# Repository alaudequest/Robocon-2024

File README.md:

# Giới thiệu

Đế robot điều khiển 4 cụm bánh Swerve bằng chuẩn truyền thông CAN bus, mỗi cụm bánh bao gồm 1 bánh BLDC điều khiển đế robot tiến lùi và 1 động cơ DC dùng để xoay góc được điều khiển bởi node CAN STM32F103C8T6, các cụm bánh sẽ nhận lệnh từ node CAN main STM32F407VET để điều khiển hai động cơ

# Version (3.0.0)

Tài liệu hiện tại tương thích với version 3.x

README cụm bánh Swerve [NodeSwerve_F103](NodeSwerve_F103/README.md)

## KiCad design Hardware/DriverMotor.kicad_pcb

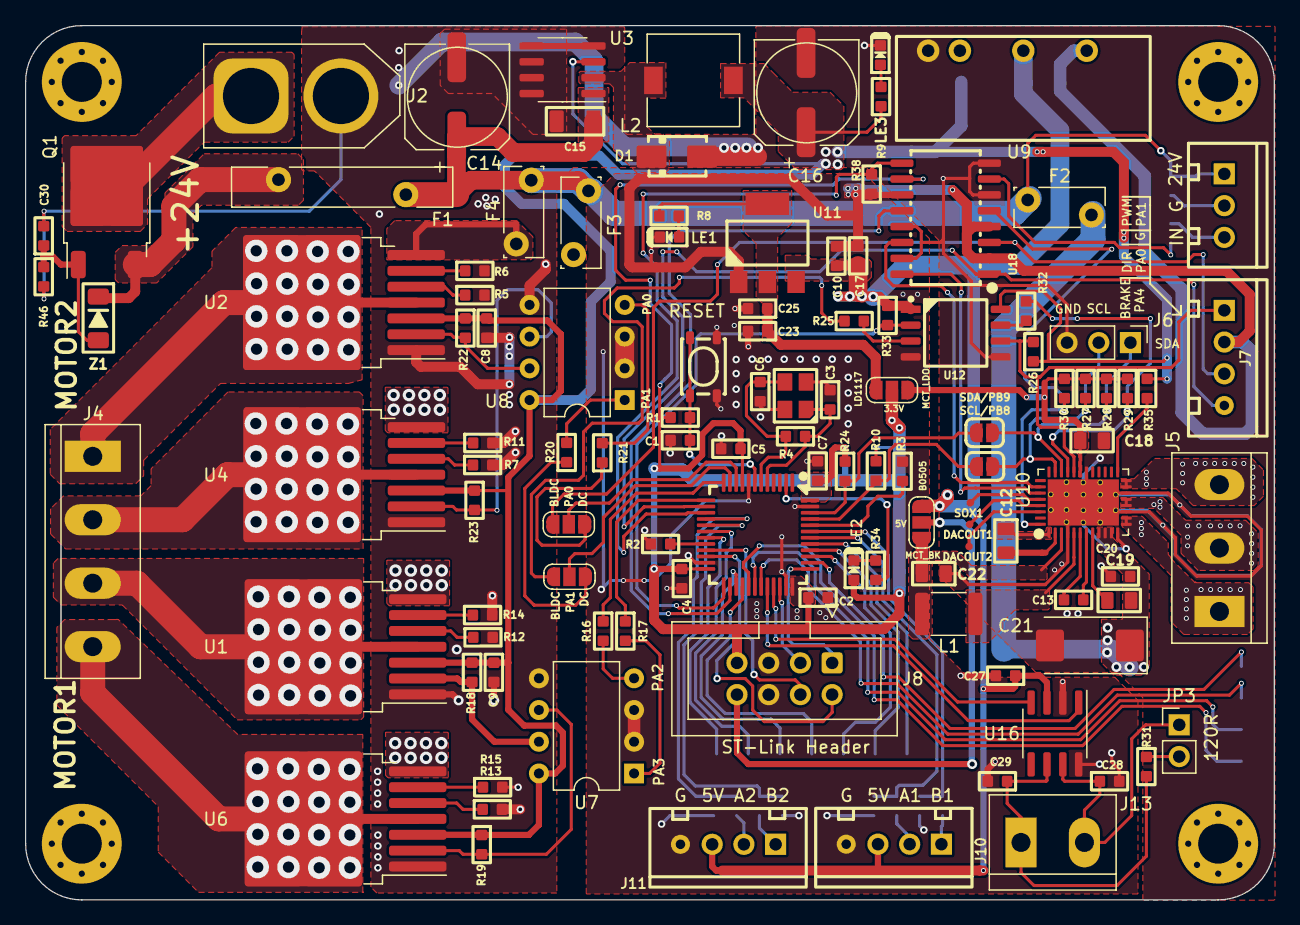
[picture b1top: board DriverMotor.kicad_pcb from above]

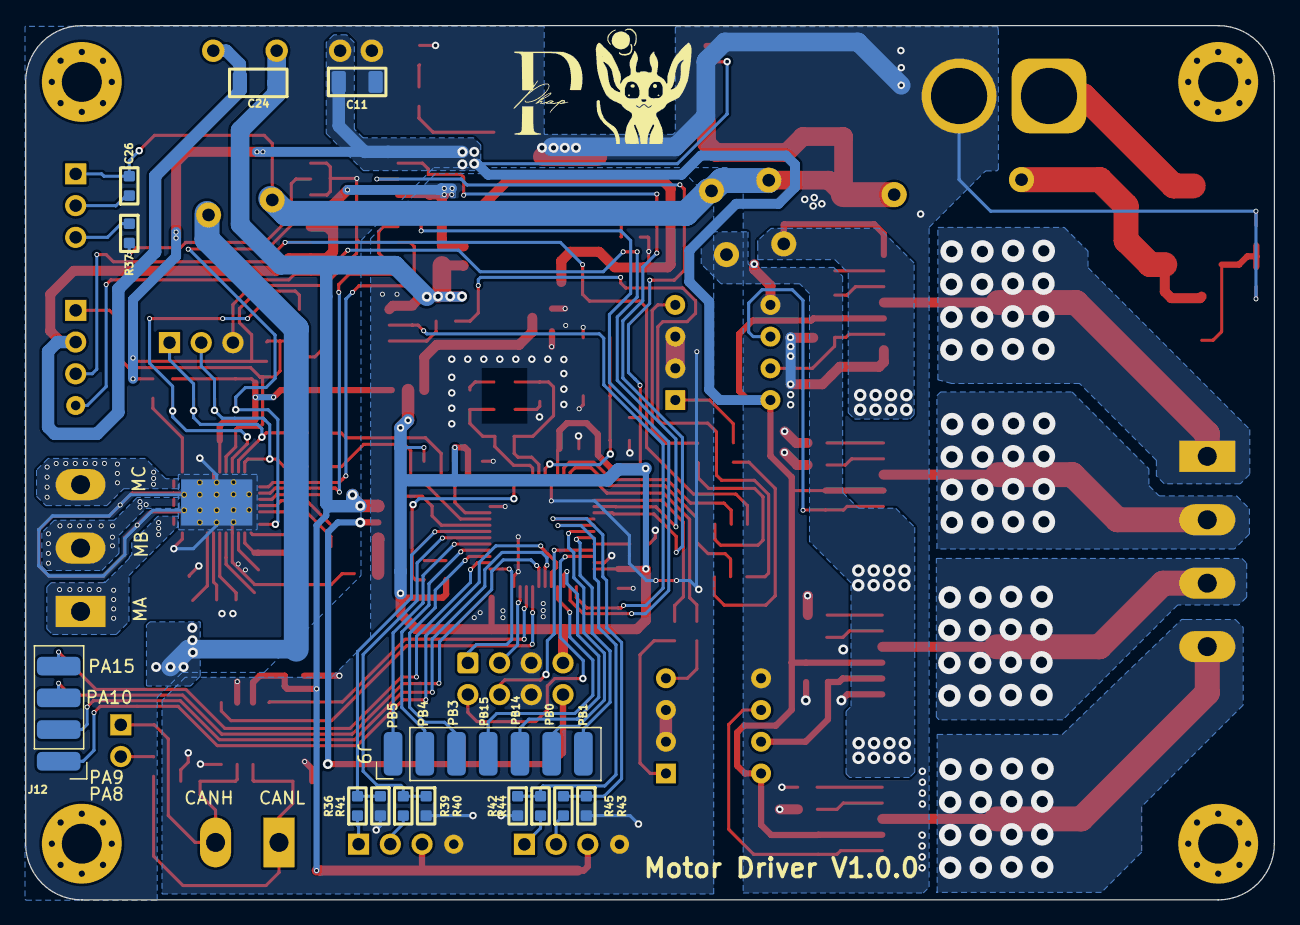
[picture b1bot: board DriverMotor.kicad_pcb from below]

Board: 2 copper layers, 100.0 x 70.0 mm, 130 parts (14 on the bottom side), 113 nets.

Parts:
C1: 10pF; C_0603
C2, C4, C5, C7, C8, C9, C10, C20, C25, C27, C30: 100nF; C_0603
C3, C6: 22pF; C_0603
C11: 4.7uF/16V; C_1206
C12, C18, C19, C22: 1uF; C_0805
C13: 47nF; C_0603
C14: 220uF/35V; CP-Alu-SMD-8x10.5mm
C15: 1uF; C_1206
C16: 470uF/16V; CP-Alu-SMD-8x10.5mm
C17, C23, C26: 10uF; C_0603
C21: 22uF/25V; CP_EIA-7343-15_Kemet-W_Pad2.25x2.55mm_HandSolder
C24: 10uF/10V; C_1206
C28, C29: 30pF; C_0603
D1: D_Diode; Package-Diode-D_SMA
DACOUT1, DACOUT2: TestPoint; TestPoint_Pad_D1.0mm
F1: 30V/5A; Fuse_Bourns_MF-RHT1000
F2: 30V/3A; Fuse_Bourns_MF-RG300
F3, F4: 30V/1.1A; Fuse_Bourns_MF-RG300
H1, H2, H3, H4: MountingHole; MountingHole_3.2mm_M3_Pad_Via
J1: Conn_01x03_Pin; Conn-Vert-THT-3P-2.54mm-S3B_XH_SM4_TB
J2: Screw_Terminal_01x02; Conn-Vert-THT-2P-7.20mm-XT60_F
J4: Screw_Terminal_01x04; TerminalBlock_bornier-4_P5.08mm
J5: Screw_Terminal_01x03; TerminalBlock_bornier-3_P5.08mm
J6: Screw_Terminal_01x03; PinHeader_1x03_P2.54mm_Vertical
J7: Conn_01x04_Male; Conn-Vert-THT-4P-2.54mm-S4B_XH_SM4_TB
J8: Conn_02x04_Odd_Even; IDC-Header_2x04_P2.54mm_Vertical
J9: Conn_01x07_Pin; Conn-Horz-SMD-7P-2.54mm-PinHeader
J10, J11: Screw_Terminal_01x04; Conn-Vert-THT-4P-2.54mm-S4B_XH_SM4_TB
J12: Conn_01x04_Male; Conn-Horz-SMD-4P-2.54mm-PinHeader
J13: Screw_Terminal_01x02; TerminalBlock_bornier-2_P5.08mm
JP3: SolderJumper_2_Open; PinHeader_1x02_P2.54mm_Vertical
L1: 47uH; L_1812_4532Metric
L2: 47uH; L_7.3x7.3_H4.5
LE1, LE2, LE3: Led; LED_0603
Q1: P_Mosfet; TO-252-2
R1, R2: 10k; R_0603
R3, R5, R6, R7, R11, R12, R13, R14, R15, R18, R19, R22, R23: 10K; R_0603
R4: 1M; R_0603
R8: 1k; R_0603
R9, R26, R33, R35, R36, R37, R38, R41, R44, R45: 1K; R_0603
R10, R24: 4k7; R_0603
R16, R17, R20, R21: 240R; R_0603
R25, R32: 330R; R_0603
R27, R28, R29, R30: 5K1; R_0603
R31: 120R; R_0603
R34: 2K2; R_0603
R39, R40, R42, R43: 2K; R_0603
R46: 100k; R_0603
S1, S2, S3, S4: SolderJump3P; SolderJumper-3_P1.3mm_Open_RoundedPad1.0x1.5mm_NumberLabels
SCL/PB8: SolderJumper_2_Open; SolderJumper-2_P1.3mm_Open_RoundedPad1.0x1.5mm
SDA/PB9: SolderJumper_2_Open; SolderJumper-2_P1.3mm_Open_RoundedPad1.0x1.5mm
SOX1: TestPoint; TestPoint_Pad_D1.0mm
SW1: SW_Push; ButtonPush-Vert-SMD-4P-SPST_PTS810
U1, U2, U4, U6: TO-263-7_TabPin8
U3: XL1509-5.0; SOIC-8_3.9x4.9mm_P1.27mm
U5: MCU_STM32F103C8Tx; Package-IC-LQFP-48P-7x7mm-P0.5mm
U7, U8: HCPL-2631; DIP-8_W7.62mm
U9: B0505S; PowerSupply-DCDC-Isolate-2W-BxxxxS
U10: MCT8316; VQFN-40-1EP_7x7mm_P0.5mm_EP5.7x3.7mm_ThermalVias
U11: LD1117; SOT233
U12: ISO7721DR; SOIC-8_5.23x5.23mm_P1.27mm
U16: TJA1051T; SOIC-8_3.9x4.9mm_P1.27mm
U18: SOIC-16W_5.3x10.2mm_P1.27mm
Y1: 8Mhz; Crystal-SMD-4P-3.2x2.6mm-3225
Z1: 15V; Package-Diode-D_MiniMELF

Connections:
+3V3: C23.1, C25.1, R8.1, S2.1, U11.2 (VO)
+5V: C10.1, C17.1, C24.1, C27.1, J10.3, J11.3, R33.1, S1.1, U9.4 (Vout), U11.3 (VI), U12.1 (VCC1), U16.3 (VCC)
+5VA: J8.8, S1.2
+24V: J2.1, Q1.2 (D)
/BTS7960/+5V_CS: C8.1, C9.1, C11.1, C16.1, L2.1, R9.1, R18.1, R19.1, R22.1, R23.1, R26.1, R35.1, U1.3 (INH), U2.3 (INH), U3.3 (FB), U4.3 (INH), U6.3 (INH), U7.8 (VCC), U8.8 (VCC), U9.2 (Vin), U12.8 (VCC2)
/BTS7960/+24V_CS: C14.1, C15.1, C26.2, F1.2, F2.1, F3.1, F4.1, J1.1, U3.1 (VIN)
/BTS7960/+24V_M1: F3.2, U1.7 (VS), U6.7 (VS)
/BTS7960/+24V_M2: F4.2, U2.7 (VS), U4.7 (VS)
/BTS7960/BTS.PWM_L1: R17.1, U5.13 (PA3/USART2_RX/ADC12_IN3/TIM2_CH4)
/BTS7960/BTS.PWM_L2: R20.1, S3.1
/BTS7960/BTS.PWM_R1: R16.1, U5.12 (PA2/USART2_TX/ADC12_IN2/TIM2_CH3)
/BTS7960/BTS.PWM_R2: R21.1, S4.1
/BTS7960/En.EnA_1: R40.1, R41.2, U5.42 (PB6/USART1_TX/I2C1_SCL/TIM4_CH1)
/BTS7960/En.EnA_2: R43.1, R45.2, U5.16 (PA6/SPI1_MISO/ADC12_IN6/TIM3_CH1)
/BTS7960/En.EnB_1: R36.2, R39.1, U5.43 (PB7/USART1_RX/I2C1_SDA/TIM4_CH2)
/BTS7960/En.EnB_2: R42.1, R44.2, U5.17 (PA7/SPI1_MOSI/ADC12_IN7/TIM3_CH2)
/BTS7960/Motor_L1: J4.3, U1.4 (OUT), U1.8 (TAB)
/BTS7960/Motor_L2: J4.1, U2.4 (OUT), U2.8 (TAB)
/BTS7960/Motor_R1: J4.4, U6.4 (OUT), U6.8 (TAB)
/BTS7960/Motor_R2: J4.2, U4.4 (OUT), U4.8 (TAB)
/BTS7960/PWM_DC_L1: R18.2, U1.2 (IN), U7.7 (VO1)
/BTS7960/PWM_DC_L2: R22.2, U2.2 (IN), U8.7 (VO1)
/BTS7960/PWM_DC_R1: R19.2, U6.2 (IN), U7.6 (VO2)
/BTS7960/PWM_DC_R2: R23.2, U4.2 (IN), U8.6 (VO2)
/MCT8316/+3V3_MCU: C2.1, C4.1, C5.1, C7.1, J8.7, LE2.1, R1.1, R10.1, R24.1, S2.2, U5.9 (VDDA), U5.24 (VDD), U5.36 (VDD), U5.48 (VDD), U18.10
/MCT8316/AVDD: C18.1, R27.1, R28.1, R29.1, R30.1, S2.3, U10.27 (AVDD)
/MCT8316/BUCK: C22.2, L1.1, S1.3, U10.3 (FB_BK)
/MCT8316/DVDD: C12.1, U10.1 (DVDD)
/MCT8316/MA: J5.1, U10.13 (OUTA), U10.14 (OUTA)
/MCT8316/MB: J5.2, U10.16 (OUTB), U10.17 (OUTB)
/MCT8316/MC: J5.3, U10.19 (OUTC), U10.20 (OUTC)
/MCT8316/MCT.BRAKE: J7.4, U5.14 (PA4/SPI1_NSS/USART2_CK/ADC12_IN4), U18.1
/MCT8316/MCT.DIR: J7.3, S4.3, U18.3
/MCT8316/MCT.FAULT: U5.26 (PB13/SPI2_SCK/USART3_CTS/TIM1_CH1N), U18.12
/MCT8316/MCT.FG: R33.2, U5.25 (PB12/SPI2_NSS/I2C2_SMBAI/USART3_CK/TIM1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), U12.2 (OUTA)
/MCT8316/MCT.PWM: R25.1, S3.3
/MCT8316/MCT.SCL: R10.2, SCL/PB8.1 (A), U5.45 (PB8/TIM4_CH3/I2C1_SCL/CANRX)
/MCT8316/MCT.SDA: R24.2, SDA/PB9.1 (A), U5.46 (PB9/TIM4_CH4/I2C1_SDA/CANTX)
/MCT8316/MCT_BRAKE: U10.35 (BRAKE), U18.16
/MCT8316/MCT_DACOUT1: DACOUT1.1, U10.37 (DACOUT1)
/MCT8316/MCT_DACOUT2: DACOUT2.1, U10.38 (DACOUT2)
/MCT8316/MCT_DIR: U10.34 (DIR), U18.14
/MCT8316/MCT_FAULT: R30.2, U10.40 (nFAULT), U18.5
/MCT8316/MCT_FG: R29.2, R32.2, U10.29 (FG)
/MCT8316/MCT_SCL: J6.2, R27.2, SCL/PB8.2 (B), U10.31 (SCL)
/MCT8316/MCT_SDA: J6.1, R28.2, SDA/PB9.2 (B), U10.30 (SDA)
/MCT8316/MCT_SOX: SOX1.1, U10.36 (DACOUT2/SOX)
/MCT8316/PA5: R38.1, U5.15 (PA5/SPI1_SCK/ADC12_IN5), U18.9
/MCT8316/PWM_BLDC: J7.1, R26.2, U10.28 (SPEED/WAKE), U12.6 (OUTB)
/MCT8316/SW_BUCK: L1.2, U10.5 (SW_BK)
/MCT8316/VM: C19.2, C20.2, C21.1, F2.2, U10.9 (VM), U10.10 (VM), U10.11 (VM)
/Power Supply/S: F1.1, Q1.3 (S), Z1.2
/Power Supply/XL1509_OUT: D1.2, L2.2, U3.2 (OUT)
/STM32F103/CANRX: U5.32 (PA11/USART1_CTS/CANRX/USBDM/TIM1_CH4), U16.1 (TXD)
/STM32F103/CANTX: U5.33 (PA12/USART1_RTS/CANTX/USBDP/TIM1_ETR), U16.4 (RXD)
/STM32F103/MCU_PA0: S4.2, U5.10 (PA0/WKUP/USART2_CTS/ADC12_IN0/TIM2_CH1_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)
/STM32F103/MCU_PA1: S3.2, U5.11 (PA1/USART2_RTS/ADC12_IN1/TIM2_CH2)
/STM32F103/OSC_IN: C3.2, R4.1, U5.5 (PD0/OSC_IN), Y1.1
/STM32F103/OSC_OUT: C6.1, R4.2, U5.6 (PD1/OSC_OUT), Y1.3
/STM32F103/PA8: J12.1, U5.29 (PA8/USART1_CK/TIM1_CH1/MCO)
/STM32F103/PA9: J12.2, U5.30 (PA9/USART1_TX/TIM1_CH2)
/STM32F103/PA10: J12.3, U5.31 (PA10/USART1_RX/TIM1_CH3)
/STM32F103/PA15: J12.4, U5.38 (PA15/JTDI)
/STM32F103/PB0: J9.6, U5.18 (PB0/ADC12_IN8/TIM3_CH3/TIM1_CH2N)
/STM32F103/PB1: J9.7, U5.19 (PB1/ADC12_IN9/TIM3_CH4/TIM1_CH3N)
/STM32F103/PB3: J9.3, U5.39 (PB3/JTDO/TIM2_CH2/TRACESWO/SPI1_SCK)
/STM32F103/PB4: J9.2, U5.40 (PB4/JNTRST/TIM3_CH1/SPI1_MISO)
/STM32F103/PB5: J9.1, U5.41 (PB5/TIM3_CH2/SPI1_MOSI/I2C1_SMBAI)
/STM32F103/PB14: J9.5, U5.27 (PB14/SPI2_MISO/USART3_RTS/TIM1_CH2N)
/STM32F103/PB15: J9.4, U5.28 (PB15/SPI2_MOSI/TIM1_CH3N)
/STM32F103/PC13: R34.2, U5.2 (PC13/TAMPER-RTC)
/STM32F103/RST: C1.2, R1.2, SW1.1, U5.7 (NRST)
/STM32F103/RX_LOG: J8.2, U5.22 (PB11/I2C2_SDA/USART3_RX/TIM2_CH4)
/STM32F103/SWCLK: J8.1, U5.37 (PA14/JTCK/SWCLK)
/STM32F103/SWDIO: J8.3, U5.34 (PA13/JTMS/SWDIO)
/STM32F103/TX_LOG: J8.4, U5.21 (PB10/I2C2_SCL/USART3_TX/TIM2_CH3)
/TJA1050/CANH: C28.1, J13.2, JP3.1 (A), U16.7 (CANH)
/TJA1050/CANL: C29.1, J13.1, R31.2, U16.6 (CANL)
GND: C1.1, C2.2, C3.1, C4.2, C5.2, C6.2, C7.2, C10.2, C17.2, C23.2, C24.2, C25.2, C27.2, C28.2, C29.2, J7.2, J8.5, J8.6, J10.4, J11.4, LE1.2, R2.1, R3.1, R38.2, R39.2, R40.2, R42.2, R43.2, SW1.2, U5.8 (VSSA), U5.23 (VSS), U5.35 (VSS), U5.47 (VSS), U7.2 (C1), U7.3 (C2), U8.2 (C1), U8.3 (C2), U9.3 (GNDout), U11.1 (GND), U12.4 (GND1), U16.2 (GND), U16.8 (S), U18.2, U18.4, U18.11, Y1.2, Y1.4
GNDD: C8.2, C9.2, C11.2, C14.2, C15.2, C16.2, C18.2, C20.1, C21.2, C22.1, C30.2, D1.1, J2.2, J6.3, LE3.2, R5.2, R6.2, R7.2, R11.2, R12.2, R13.2, R14.2, R15.2, R46.2, U1.1 (GND), U2.1 (GND), U3.4 (~EN), U3.5 (GND), U3.6 (GND), U3.7 (GND), U3.8 (GND), U4.1 (GND), U6.1 (GND), U7.5 (GND), U8.5 (GND), U9.1 (GNDin), U10.4 (GND_BK), U10.12 (PGND), U10.15 (PGND), U10.18 (PGND), U10.26 (AGND), U10.41 (ThermalPad), U12.5 (GND2), U18.6, U18.8, U18.13, U18.15
unnamed: C26.1, J1.2
unnamed: J1.3, R37.1
unnamed: J10.1, R36.1
unnamed: J10.2, R41.1
unnamed: J11.1, R44.1
unnamed: J11.2, R45.1
unnamed: JP3.2 (B), R31.1
unnamed: LE1.1, R8.2
unnamed: LE2.2, R34.1
unnamed: LE3.1, R9.2
unnamed: C30.1, Q1.1 (G), R46.1, Z1.1
unnamed: R37.2, U18.7
unnamed: R14.1, U1.6 (IS)
unnamed: R12.1, U1.5 (SR)
unnamed: R6.1, U2.6 (IS)
unnamed: R5.1, U2.5 (SR)
unnamed: R11.1, U4.6 (IS)
unnamed: R7.1, U4.5 (SR)
unnamed: R3.2, U5.44 (BOOT0)
unnamed: R2.2, U5.20 (PB2/BOOT1)
unnamed: R15.1, U6.6 (IS)
unnamed: R13.1, U6.5 (SR)
unnamed: R17.2, U7.1 (A1)
unnamed: R16.2, U7.4 (A2)
unnamed: R20.2, U8.1 (A1)
unnamed: R21.2, U8.4 (A2)
unnamed: C19.1, U10.8 (CP)
unnamed: C13.2, U10.7 (CPH)
unnamed: C13.1, U10.6 (CPL)
unnamed: C12.2, U10.2 (DGND)
unnamed: R35.2, U10.21 (DRVOFF)
unnamed: R32.1, U12.7 (INA)
unnamed: R25.2, U12.3 (INB)

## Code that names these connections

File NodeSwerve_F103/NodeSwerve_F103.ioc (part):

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Mcu.Name=STM32F103C(8-B)Tx
Mcu.Package=LQFP48
Mcu.UserName=STM32F103C8Tx
PA0-WKUP.GPIOParameters=GPIO_Label
PA0-WKUP.GPIO_Label=BLDC_DIR
PA0-WKUP.Signal=GPIO_Output
PA1.Signal=S_TIM2_CH2
PA10.Mode=Asynchronous
PA10.Signal=USART1_RX
PA11.Mode=CAN_Activate
PA11.Signal=CAN_RX
PA12.Mode=CAN_Activate
PA12.Signal=CAN_TX
PA13.Mode=Serial_Wire
PA13.Signal=SYS_JTMS-SWDIO
PA14.Mode=Serial_Wire
PA14.Signal=SYS_JTCK-SWCLK
PA2.Signal=S_TIM2_CH3
PA3.Signal=S_TIM2_CH4
PA4.GPIOParameters=GPIO_Label
PA4.GPIO_Label=BLDC_BRAKE
PA4.Signal=GPIO_Output
PA5.GPIOParameters=GPIO_Label
PA5.GPIO_Label=Sensor_Home
PA5.Signal=GPIO_Input
PA6.Signal=S_TIM3_CH1
PA7.Signal=S_TIM3_CH2
PA9.Mode=Asynchronous
PA9.Signal=USART1_TX
PB3.GPIOParameters=GPIO_Label
PB3.GPIO_Label=UserLED
PB3.Signal=GPIO_Output
PB6.Signal=S_TIM4_CH1
PB7.Signal=S_TIM4_CH2
PD0-OSC_IN.Mode=HSE-External-Oscillator
PD0-OSC_IN.Signal=RCC_OSC_IN
PD1-OSC_OUT.Mode=HSE-External-Oscillator
PD1-OSC_OUT.Signal=RCC_OSC_OUT
RCC.SYSCLKFreq_VALUE=72000000
RCC.SYSCLKSource=RCC_SYSCLKSOURCE_PLLCLK
board=custom

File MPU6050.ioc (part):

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Mcu.Name=STM32F103C(8-B)Tx
Mcu.Package=LQFP48
Mcu.UserName=STM32F103C8Tx
PA10.Mode=Asynchronous
PA10.Signal=USART1_RX
PA13.Mode=Serial_Wire
PA13.Signal=SYS_JTMS-SWDIO
PA14.Mode=Serial_Wire
PA14.Signal=SYS_JTCK-SWCLK
PA9.Mode=Asynchronous
PA9.Signal=USART1_TX
PB0.GPIOParameters=GPIO_Label
PB0.GPIO_Label=Ready
PB0.Signal=GPIO_Output
PB1.GPIOParameters=GPIO_Label
PB1.GPIO_Label=Data
PB1.Signal=GPIO_Output
PB13.GPIOParameters=GPIO_Label
PB13.GPIO_Label=UserGreenLED
PB13.Signal=GPIO_Output
PB14.Mode=PWM Generation2 CH2N
PB14.Signal=TIM1_CH2N
PB5.GPIOParameters=GPIO_Label,GPIO_ModeDefaultEXTI
PB5.GPIO_Label=UserBtn
PB5.GPIO_ModeDefaultEXTI=GPIO_MODE_IT_FALLING
PB5.Signal=GPXTI5
PB6.Mode=I2C
PB6.Signal=I2C1_SCL
PB7.Mode=I2C
PB7.Signal=I2C1_SDA
PB8.GPIOParameters=GPIO_Label
PB8.GPIO_Label=MPU_INT
PB8.Signal=GPXTI8
PD0-OSC_IN.Mode=HSE-External-Oscillator
PD0-OSC_IN.Signal=RCC_OSC_IN
PD1-OSC_OUT.Mode=HSE-External-Oscillator
PD1-OSC_OUT.Signal=RCC_OSC_OUT
RCC.SYSCLKFreq_VALUE=72000000
RCC.SYSCLKSource=RCC_SYSCLKSOURCE_PLLCLK
board=custom

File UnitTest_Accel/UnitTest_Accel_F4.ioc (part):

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Mcu.Name=STM32F407V(E-G)Tx
Mcu.Package=LQFP100
Mcu.UserName=STM32F407VETx
PA13.Mode=Serial_Wire
PA13.Signal=SYS_JTMS-SWDIO
PA14.Mode=Serial_Wire
PA14.Signal=SYS_JTCK-SWCLK
PA15.Signal=S_TIM2_CH1_ETR
PA2.Signal=S_TIM5_CH3
PA3.Signal=S_TIM5_CH4
PA8.Signal=S_TIM1_CH1
PA9.Signal=S_TIM1_CH2
PB3.Signal=S_TIM2_CH2
PE14.GPIOParameters=GPIO_PuPd,GPIO_Label
PE14.GPIO_Label=Checkpoint
PE14.GPIO_PuPd=GPIO_PULLUP
PE14.Signal=GPXTI14
PH0-OSC_IN.Mode=HSE-External-Oscillator
PH0-OSC_IN.Signal=RCC_OSC_IN
PH1-OSC_OUT.Mode=HSE-External-Oscillator
PH1-OSC_OUT.Signal=RCC_OSC_OUT
RCC.HSE_VALUE=8000000
RCC.SYSCLKFreq_VALUE=168000000
RCC.SYSCLKSource=RCC_SYSCLKSOURCE_PLLCLK
board=custom

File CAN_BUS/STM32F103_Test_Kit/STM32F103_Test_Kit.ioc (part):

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Mcu.Name=STM32F103C(8-B)Tx
Mcu.Package=LQFP48
Mcu.UserName=STM32F103C8Tx
PA13.Mode=Serial_Wire
PA13.Signal=SYS_JTMS-SWDIO
PA14.Mode=Serial_Wire
PA14.Signal=SYS_JTCK-SWCLK
PB8.Signal=S_TIM4_CH3
PB9.Signal=S_TIM4_CH4
PC13-TAMPER-RTC.GPIOParameters=GPIO_Label
PC13-TAMPER-RTC.GPIO_Label=USER_LED
PC13-TAMPER-RTC.Signal=GPIO_Output
PD0-OSC_IN.Mode=HSE-External-Oscillator
PD0-OSC_IN.Signal=RCC_OSC_IN
PD1-OSC_OUT.Mode=HSE-External-Oscillator
PD1-OSC_OUT.Signal=RCC_OSC_OUT
RCC.SYSCLKFreq_VALUE=72000000
RCC.SYSCLKSource=RCC_SYSCLKSOURCE_PLLCLK
board=custom

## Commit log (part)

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2023-11-18 Update node F1: remove function pointer of SetHome
2023-11-18 Updated 19/11/2023
2023-11-19 Test event group OK
2023-11-19 Initial Function of Odometry
2023-11-19 Update: F4 measure processing time of function RTR_SpeedAngle from begin to end
2023-11-20 First function of Swerve Odometry
2023-11-23 Test eventgroup to send and receive 1 node once time, repeat 4 times with total time is 1.1ms, slower than for loop of NOP, reverse for future use
2023-11-24 Add CAN_RTR_Encx4BLDC_AngleDC for RTR encoder X4 count of BLDC and AngleDC, not use CAN_SpeedBLDC_AngleDC because the affect to input Motor API, ignore language setting xml
2023-11-28 build MPU6050 lib.cpp with write and read method, test WHO_AM_I register OK, can not read temperature value
2023-11-28 fix: method Write, can read temperature data and config sensor registers
2023-11-29 Update + feature: change method name of MPU, add get set clock source
2023-11-29 Adding ConfigRegister struct to save config MPU data after init, easy to dev methods of MPU6050 config register, can be read GyroZ data by changing clock source from internal to PLL_XGYRO
2023-11-30 feature: Read Raw each axis and 6 axis OK
2023-11-30 Change offset not affect much
2023-12-01 Adding UART to send to PC in main.cpp, remove this pointer of class MPU6050 in MPU6050.h
2023-12-02 add this->i2c instead of i2c in MPU::init
2023-12-03 nothing
2023-12-06 Update: Seperate CANCTRL_MODE_MOTOR_SPEED_ANGLE and CANCTRL_MODE_NODE_REQ_SPEED_ANGLE, update README for RTR mode
    CAN_FuncHandle:
    + Thêm cặp hàm Get/Set EncoderX4CountBLDC_Angle
    CAN_Control:
    + Thay đổi thứ tự các ID trong bộ lọc list để khớp với datasheet
    BoardParameter:
    + Xóa hàm brd_GetCurrentCountBLDC()
2023-12-08 Add LogPort class to use template for plotter
2023-12-09 Update: get 6 axis, calib raw accel
2023-12-13 Update: Can read FIFO interrupt, not handle properly
    - Adding Timer 2, not use yet
    - fifoHandle not optimize, temporary use to test interrupt feature
2023-12-25 Done with odometry and Forward kinematic
2024-01-13 Update: Config pinout
2024-01-13 Add project Actuator_GetShootingBall
2024-01-13 Add .gitignore
2024-01-15 remove test project
2024-01-17 Update: Add and config Encoder library. Issues: Encoder library not support for interrupt type -> need to rewrite.
2024-01-17 Update: Config new pinout and commented issues
2024-01-17 Done point to point algorithm
2024-01-17 Setup pwm Channel in BoardParameter lib
2024-01-18 Bug Encoder Gun 1
2024-01-19 First commit, not use old board, commit to switch to other branch
2024-01-19 worked pure pursuilt algorithm
2024-01-20 test shoot without PID
2024-01-20 Trajec Planning function
2024-01-21 Issue: Cấp xung pwm cho động cơ bắn nhưng đông cơ không quay (bts hỏng) Update: Thêm điều kiện để quay rulo bóng và rulo súng
2024-01-21 NamDHay
2024-01-22 Add get&set value function
2024-01-22 new actuator mergre
2024-01-22 fix HardFault Handle
2024-01-23 Done 1 turn get wheeds
2024-01-23 Up-to-date Valve trigger and shooting ball, control robot to catch and drop seedling
2024-01-23 New feature: Seperate encoder mode and interrupt
2024-01-23 Add encoder init to brd_Init
2024-01-23 get wheed two turns
2024-01-23 MPU read ok
2024-01-23 Add BNO08x Arduino to project, remove unesscessary files
2024-01-24 Fix a few type errors
2024-01-24 Complete
2024-01-24 Complete low level Driver
2024-01-24 Successfully read and write to app
2024-01-24 steady V1
2024-01-25 ignore .vscode
2024-01-25 Need to update
2024-01-26 Update IMU code
2024-01-26 Update: add command list, AppProtocol and ParamPID struct
2024-01-26 Update: PD_On and Off, merging 50f13e65 commit from origin HoangTrajecPlanning branch
2024-01-26 Add CAN_FuncHandle
2024-01-27 Steady V2
2024-01-28 Still unstable
2024-01-30 BNO DMA
2024-02-01 Pose estimation
2024-02-01 Sai cmnr
2024-02-03 Add Gun Parameter and function handle
2024-02-03 Add RTR Handle and Shoot queue
2024-02-04 Add function to control rulo get balls and stop all motor on gun module
2024-02-04 Complete control motor part -> need to test CANBus
2024-02-06 Steady before add shoot
2024-02-06 Move CAN lib to main F407
2024-02-06 Add Cmake
2024-02-06 Update new function
2024-02-07 Change name AppProtocol to FrameData, update small change
2024-02-07 Remove unused ID
2024-02-07 remove vscode
2024-02-07 SteadyShoot
2024-02-08 Steady and shoot
2024-02-08 Update CAN folder from HoangSteadyV2
2024-02-08 2ndShoot
2024-02-10 Steady Mung 1
2024-02-18 Last update at Release frist wheed
2024-02-18 Add Break to serveral case
2024-02-18 Small Fixed for estimation
2024-02-22 Remove Rotary DC and add software timer to calculate PID
2024-02-25 Fix Stupid defined and if condition
2024-02-25 Remove software timer function and use xTaskGetTickCount to make delay
2024-02-26 Small clean
2024-02-28 small change
2024-03-14 Code work with Phat
2024-03-15 fix: remove language.settings and change cal_absF to static
2024-03-16 Get and Put Ball on AutoRobot
2024-03-17 Refactor: trajectory plainning library and manual set, not compile yet
2024-03-18 docs: move LogData to new folder Communication, add example code
2024-03-18 feat: ParameterSetting and config path to inc and src of Communication folder to project
2024-03-18 fix: QueueReceive, increase osDelay in InverseKinematic task
2024-03-18 fix: increase OdoHandle task stack size to 256 prevent stack overflow, test success Trajectory and Manual Set with 3 settings
2024-03-20 Add PE12 Forklift sensor interrupt
2024-03-20 Refactor BallTransferToSilo from PutBall module
2024-03-20 7 out of 10 ball sucessed
2024-03-21 feat: add HAL_TIM_start for pwm and encoder channel, add func get encoderX4 from forklift encoder
2024-03-21 add UART2, pwm channel and encoder for forklift motor and rulo, change name task RTOS, test actuator robot2
2024-03-21 GetBall Succeed 90%
2024-03-22 Update GetBall
2024-03-23 Update: change process control API to chassis control API
2024-03-23 FloatingEncOk
2024-03-23 Code a Loc train
2024-03-24 feat <Robot1_Gun_Actuator>:Add Shootball handle to Main_F407 and test case for it
2024-03-24 clean up all task, prepare to code Actuator task
2024-03-24 Add sensor interrupt config from cubeMX
2024-03-24 feat: add NVIC config for sensor ball push up
2024-03-24 update: test both arm catch and release rice
2024-03-24 Chu trinh lay 2 trai banh hoi on dinh
2024-03-24 fix: can not control bts
2024-03-24 feat <Robot1_Gun&BallConveyor>: Acceleration gun
2024-03-24 Steady get 2 ball and backhome
2024-03-25 Done kinematic
2024-03-25 Get 2 Ball 95%
2024-03-26 Succeed Merge PutBall and Sensor ADC
2024-03-27 PID with A Loc
2024-03-28 Updated code with a Loc
2024-03-28 Code skeleton
2024-03-28 fix : remove Actuator_GetShootBall
2024-03-28 remove unnecessary file
2024-03-30 Link new library to F1 project
2024-03-30 feat: Add AppInterface library
2024-03-30 Add CRC16 and seperate AppInterface to Communication folder
2024-03-30 add ArgumentOfCommandList_t, tx and rx buffer change to pointer, fix variable name to compile code, add comments
2024-03-30 Add PID tuning for 2 guns
2024-04-01 Steady get 2 ball and back home
2024-04-02 feat: Control BLDC and DC with PID via app interface
2024-04-02 feat: adding send relay command status of board at init
2024-04-03 Optimize Angle now available at slave
2024-04-03 Clean up Algorimth code in main.c
2024-04-03 New API for point to point and Angle rotate algorithm
2024-04-04 Hoang Merge complete part 1
2024-04-04 No Hardfault update
2024-04-04 reapply app interface from node swerve, change Commandlist
2024-04-04 feat: Place init code(CAN and valve) in int main instead of each task, add valve_OutputAllPin to control by app
2024-04-04 Test valve output with app OK
2024-04-05 App check if brdID is not zero
2024-04-05 Update commandlist for node swerve
2024-04-05 Add #define board in AppInterface
2024-04-05 Add define macro for each board selected
2024-04-07 feat:turn PID off and break pin on at specific speed
2024-04-07 feat: Add CAN untangle BLDC
2024-04-07 feat: untangle bldc from app
2024-04-07 feat: add untangleBLDC feature on main.c
2024-04-07 feat: Add AngleOptimizer and fix switch case SetHome and UntangleBLDC
2024-04-08 fix library reference
2024-04-08 feat: add jumpToError, MakeFrame_2 and reset AppInterface
2024-04-08 feat: Hanlde CurrentSpeedBLDC and CurrentAngleDC hande, reset encoder count instead of turn off timer
2024-04-08 Update AppInterface module from Khoa_AppInterface_NodeSwerve branch to MainF407 project
2024-04-08 Accelerate and run at 6000rpm
2024-04-09 feat: hanlde RuloShootBall TargetSpeed
2024-04-09 Test Gun ok
2024-04-10 Added Angle Optimizer for Node
2024-04-10 Fix file in PID_Swerve module
2024-04-10 small fix for board ID
2024-04-10 small change on kinematic
2024-04-11 Fixed Angle Optimizer code
2024-04-11 Fixed Limit output for DC
2024-04-11 Added new limit for DC Swerve
2024-04-11 Add untangle for slave
2024-04-11 Add Motor and ActuatorGun library from NamDHay_Robot1_ShootBall
2024-04-11 Add buzzer
2024-04-11 Fix: pin E5 E6 to GPIO output, Start getball and stop get ball, test get ball OK
2024-04-11 feat: Add PID for rulo shooting ball, not test
2024-04-11 fixed main ADC code
2024-04-11 feat: add accel rulo speed and test with app ok
2024-04-11 Small fix for easier test code
2024-04-11 Fix Angle PID controller
2024-04-11 Add protection time
2024-04-12 Step 8
2024-04-12 Small Fix Angle Calculate kinematics
2024-04-12 Get 3 Ball
2024-04-12 feat: add Sensor module with EXTI, read sensor OK temporarily
2024-04-12 Remove some API for RB1
2024-04-12 feat: Update Sensor trigger handle
2024-04-12 fix kinematic swerve
2024-04-12 test ok some Gamepad function
2024-04-12 Get Ball
2024-04-13 Ready to merge Actuator
2024-04-13 feat: Merging code from Hoang_Robot1 branch to get process run
2024-04-13 fix valve mapping pin, valve test ok
2024-04-13 Test catch rice and shoot ball, not done
2024-04-14 STM32 Lib
2024-04-14 Success Shot 1 Ball
2024-04-14 feat: replace osDelay with Process inline function
2024-04-15 Fix submodule after checkout to other branch
2024-04-15 Test lai chu trinh
2024-04-15 Add STM32-Library submodule
2024-04-15 Remove ActuatorGetShootBall project
2024-04-16 Fix get 2 wheets
2024-04-16 fix: sethome complete buzzer on
2024-04-17 Replace VelocityCalculate to encoder_GetSpeed
2024-04-17 feat: update valve process to use in shoot ball time, in testing game pad
2024-04-17 update main.c from dev branch, update actuator task
2024-04-17 remove gunTargetSpeed in MainF4Robot1App
2024-04-17 add Chassis process
2024-04-18 Complete collect rice from area 1, next to area 2
2024-04-18 Test shootball robot 1 OK
2024-04-19 Robot 2 run pass river v1
2024-04-19 Super Speed
2024-04-19 feat: Run motor OK, speed up robot1 process
2024-04-19 feat: Add delay on row above to rotate robot
2024-04-19 slowdown
2024-04-19 Rasberry detect
2024-04-19 make process Fast
2024-04-19 Release 1 ball
2024-04-21 Slowly
2024-04-21 feat: merge NodeSwerveF103 from Khoa_AppInterface_Node branch
2024-04-21 Change config pin encoder gun 1 and pwm
2024-04-21 Success 12 Rice
2024-04-21 Success 12 Rice and go to zone 2
2024-04-22 fix: u above limit to 245, add rulo shoot speed up and down from game pad
2024-04-22 Loop of getting ball
2024-04-23 Full san V1
2024-04-23 feat: add CAN robot error mode for robot1
2024-04-23 Upd : Add U sensor test
2024-04-23 feat: buzzer beep when collect ball sensor detect and change rulo shootball speed
2024-04-24 feat: add RobotSignalButton, test OK
2024-04-24 feat: add func pointer for RobotSignalButton
2024-04-24 new path fixed for arcurracy
2024-04-24 Change RobotSignalButton pin and add 2 LED red and blue
2024-04-24 Added new protection for node
2024-04-25 new release wire
2024-04-25 Untangle wire not OK, reverse back to old version
2024-04-26 Full auto V1
2024-04-26 Demo on
2024-04-26 DOI QUY DAO
2024-04-27 not done
2024-04-27 6 Rice and 6 Ball
2024-04-28 2 san
2024-04-28 Retry chua Test
2024-04-28 test flash and custom gamepad ok
2024-04-28 Demo gamepad with flash OK
2024-04-29 Add flash and gamepad module to robot2
2024-04-29 refactor: refactor overhead in flash,feat: add ball in silo
2024-05-02 Success RED TEAM
2024-05-03 feat: PWM at init, change speed by gamepad at L1 and R1
2024-05-03 Merging flash from Hoang_Robot2_OptimizePath2 and add reset all data in flash
2024-05-04 Change shootball PID to PWM, collect ball use relay
2024-05-04 CODE THI
2024-05-04 swap 2 PWM of rulo shootball, code not test
